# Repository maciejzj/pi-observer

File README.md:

# pi-observer
A system for remote control, data acquisition and visualization for Raspberry Pi.

WIP: Moving from PHP based web stack to Pyton Flask.

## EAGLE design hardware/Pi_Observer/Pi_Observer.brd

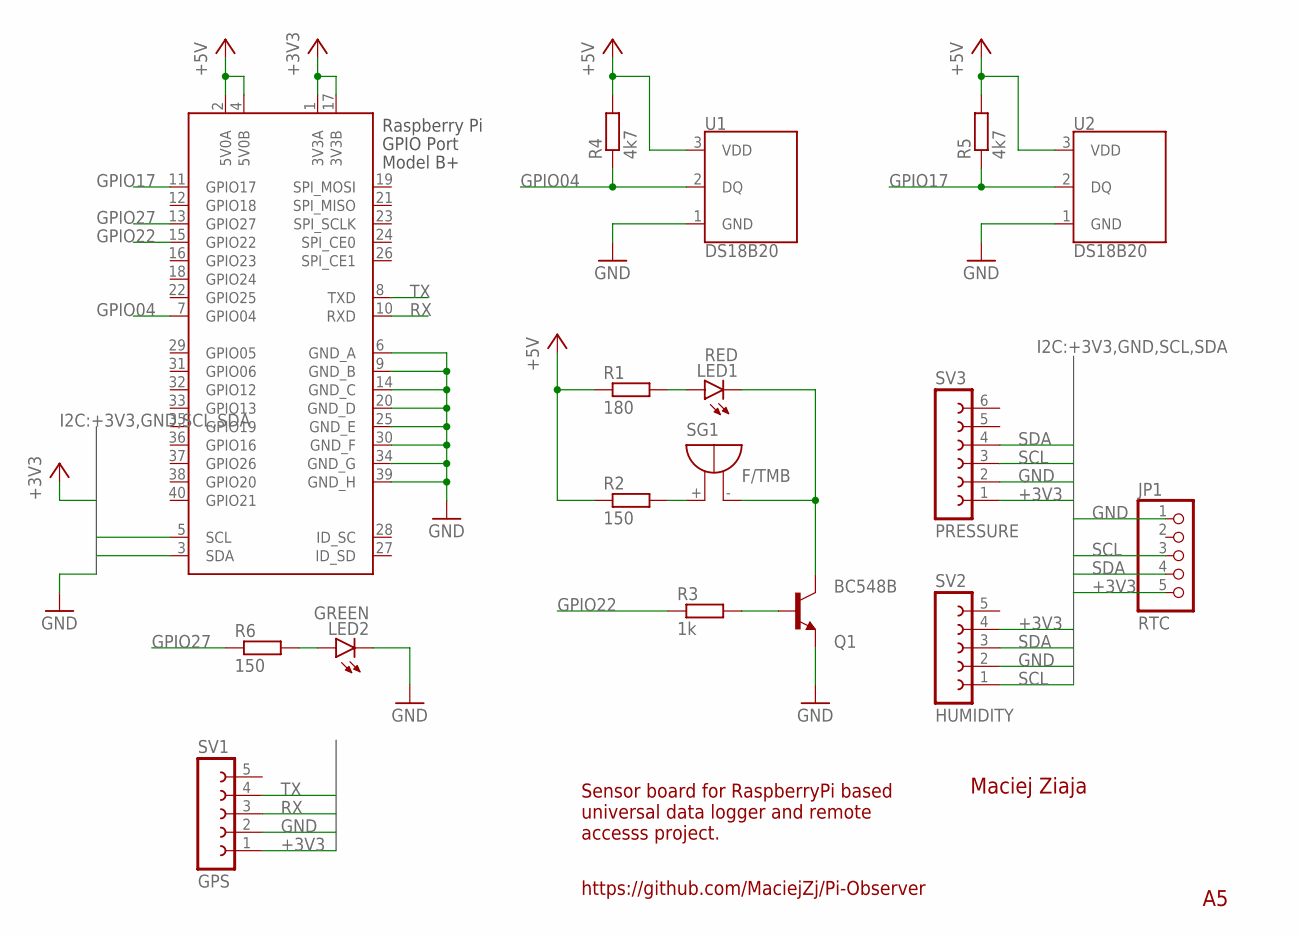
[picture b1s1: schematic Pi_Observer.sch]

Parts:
JP1: RTC; 1X05
LED1: RED; LED5MM
LED2: GREEN; LED5MM
Q1: BC548B; TO92-EBC
R1: 180; M1206
R2, R6: 150; M1206
R3: 1k; M1206
R4, R5: 4k7; M1206
SG1: F/TMB
SV1: GPS; FE05-1
SV2: HUMIDITY; FE05-1
SV3: PRESSURE; FE06
U1, U2: DS18B20; TO-92-AMMO
X1: RASPI_GPIO_B+#_PIN; RASPI_GPIO_B+_PIN

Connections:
+3V3: JP1.5, SV1.1, SV2.4, SV3.1, X1.1 (3V3A), X1.17 (3V3B)
+5V: R1.1, R2.1, R4.2, R5.2, U1.3 (VDD), U2.3 (VDD), X1.2 (5V0A), X1.4 (5V0B)
GND: JP1.1, LED2.K (C), Q1.E, SV1.2, SV2.2, SV3.2, U1.1 (GND), U2.1 (GND), X1.6 (GND_A), X1.9 (GND_B), X1.14 (GND_C), X1.20 (GND_D), X1.25 (GND_E), X1.30 (GND_F), X1.34 (GND_G), X1.39 (GND_H)
GPIO04: R4.1, U1.2 (DQ), X1.7 (GPIO04)
GPIO17: R5.1, U2.2 (DQ), X1.11 (GPIO17)
GPIO22: R3.1, X1.15 (GPIO22)
GPIO27: R6.1, X1.13 (GPIO27)
unnamed: LED1.K (C), Q1.C, SG1.-
unnamed: R2.2, SG1.+
unnamed: LED1.A, R1.2
unnamed: Q1.B, R3.2
unnamed: LED2.A, R6.2
RX: SV1.3, X1.10 (RXD)
SCL: JP1.3, SV2.1, SV3.3, X1.5 (SCL)
SDA: JP1.4, SV2.3, SV3.4, X1.3 (SDA)
TX: SV1.4, X1.8 (TXD)

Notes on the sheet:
Maciej Ziaja
https://github.com/MaciejZj/Pi-Observer
Sensor board for RaspberryPi based universal data logger and remote accesss project.

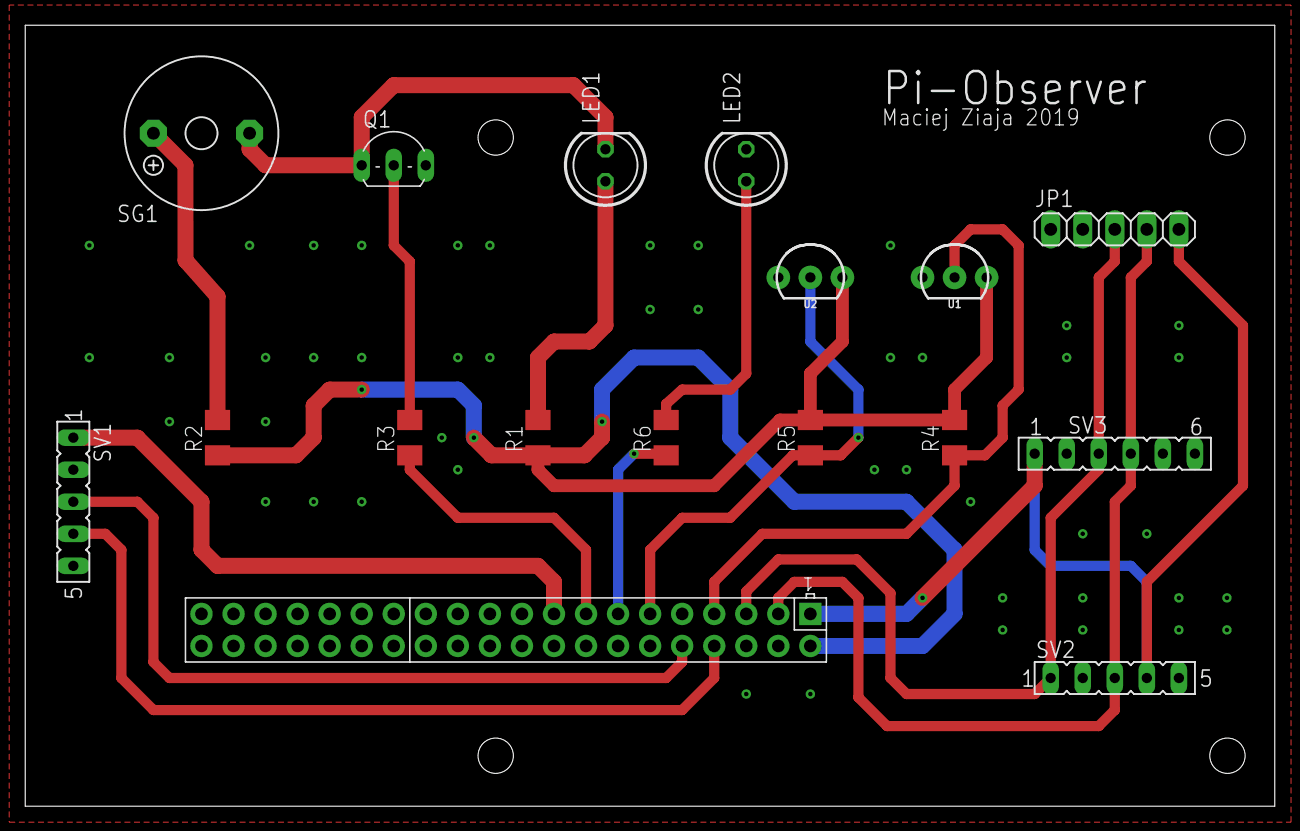
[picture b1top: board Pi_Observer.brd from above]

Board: 2 copper layers, 99.0 x 61.9 mm, 17 parts (0 on the bottom side), 16 nets.

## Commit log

2018-10-09 Imports hitherto work
2018-10-09 Creates README and .gitignore
2018-10-12 Update README.md
    Changed description of the project.
2018-10-13 Create db_setup and adds users db creation
2018-10-14 Install python sql module and setup db for logs
2018-10-14 Log pressure to sql db
2018-10-14 Log from thermometers using Python
2018-10-14 Log temperature to sql db
2018-10-14 Fix timestamp format for press alt db logging
2018-10-14 Log location to sql db
    Although this provides sql db logging functionality for all sensors, the
    gps.py is left in a messy state between old way of logging and new, iss14
    and iss11 are likely to address this problem.
    Closes: #6
2018-10-15 Remove old way of location logging
2018-10-15 Cleanup gps class
    Although this resolves cleanup issue the class may still need better error
    handling
    Resolves: #14
2018-10-15 Create separate dbs for users and sensor logs
2018-10-15 reapaired lack of semicolon - db_setup.sql -line 12 added second author's name - html/index.php created html/register.php
2018-10-16 registration with e-mail - frontend changed html/main.php - added second author's name
2018-10-16 users table in balloonS_users db changed
2018-10-16 repair - 3
2018-10-16 Display temperature log as html table
    Keep in mind that the table in not stylised so it has no borders and
    whats more important it is as long as it needs to display all records.
2018-10-16 Shorten creating tables and clean the clode
2018-10-16 Create css for tables to limit their height
2018-10-16 Move creating table to func in and make univerasal
    The function is in separate file, tables names are stored in dictionary,
    applied this method of making tables to all logs.
    Resolves: #8
2018-10-16 Import introduction report
2018-10-16 Update report of Maciej Ziaja for W2
2018-10-16 Add registration by e-mail
2018-10-18 Cleaning folders structure after report
2018-10-20 Pass JSON temp_log table from php to js
    This is clumsy now. Better way may be preparing data before drawing the
    site, then deploying it by echo() and innerHTML.
2018-10-20 Registration polish
2018-10-20 Separate making log tables and displaying them
    This enables us to process the data and pass it to js at the beggining
    of the file, instead of doing it in the middle of html site.
2018-10-20 Repair of email_confirmation.php and welcome.php
2018-10-20 Pass all logs with JSON
2018-10-21 Add forgotten hum_log JSON passing
2018-10-21 Create func for extracting plot data from JSON
2018-10-21 Create chart drawing function for hum log
2018-10-23 Maciej Ziaja report W3 and minor fixes
2018-10-23 Maciej Cholewa report W3
2018-10-28 Add double chart making for temperature
    Also ensures that internal and external temperatures are logged with
    same timestamp.
2018-10-28 Draw all charts with js
2018-10-28 Remove old way of presenting logs data
2018-10-28 Better errors handling in gps communication
2018-10-28 Add status field to location logging
2018-10-28 Extract loc data from JSON to arrays
2018-10-28 Draw google maps markers from SQL db logs
    Resolves: #22
2018-10-28 Temporary update charts css
    This will be polished in the future
2018-10-31 Stylise log tables
    This moves css to the less framework
2018-11-01 Consistent blue accent color
2018-11-01 Stylise Google Maps box
2018-11-01 Remove old buttons for downloading log files
2018-11-01 Create borders and shadows for all charts
2018-11-01 Stylise motion stream div
2018-11-01 Fix make_table calling arguments
2018-11-06 Design the tables' and charts' position on site
2018-11-08 Create new look for topbar
2018-11-08 Add new style for login page
2018-11-08 Make corners inside google maps round
2018-11-09 Cleanup the topbar
2018-11-09 Strip css for future responsive rewriting
2018-11-09 Rearrange css code order
2018-11-09 Add control panel container and description
2018-11-09 Make wrapper for gpio and strip stream css
2018-11-09 Responsive layout for single tab sections
2018-11-09 Responsvie layout for maps and controls
2018-11-09 Responsive layout for temp log
2018-11-09 Add padding for footer
2018-11-10 Fold time cell in loc table
2018-11-10 Make tablet layout for gpio and stream
2018-11-10 Remove unnecessary map canvas css wrapper
2018-11-10 Fix stream height to preserve placeholder dimensions
2018-11-10 Mobile version for charts and tables
2018-11-10 Change min width of site and fix typo
2018-11-10 Add viewport for mobile screen support
    Resolves: #29
2018-11-11 Add background svg to gpio buttons pane
2018-11-12 Apply new design to registration page
2018-11-13 Back to previous login page design
2018-11-13 Repair the orthography
2018-11-13 Add rocket to the bg graphic
2018-11-20 Make new GPIO buttons
2018-11-20 Adjust onclick on GPIO buttons
2018-11-27 Repair GPIO on off indicating
2018-11-27 Repair GPIO
2018-12-02 Repair GPIO 2
2019-01-15 Comment code
2019-01-15 Add comments to MZ part
2019-08-01 Move all comde to subfolder
2019-08-01 Add i2c setup in install script
2019-08-01 Update gitignore
2019-08-01 Add db setup, pklist and pip to install script
2019-08-02 Add hum sensor setup
2019-08-02 Update script to read from hum sensor
2019-08-02 Update temp sensor and 1 wire setup
    Also spaces in python scripts
2019-08-02 Extend 1wire setup
2019-08-06 Better align for sql setup script
2019-08-06 Setup and script press and alt log
2019-08-11 Fix gps and make it py3
2019-08-11 Add gps to installation
2019-08-11 Cleanup
2019-08-11 Fix unit in hum logger
2019-08-11 Round some log values
2019-08-11 Add rtc support and start script
2019-08-11 Fix RTC in start script
2019-08-12 Fix rtc_log location
2019-08-12 Fix date format in logs
2019-08-12 Bring chart drawer back
2019-08-12 Fix file naming and location
    Resolves: #32
2019-08-12 Extend start script
2019-08-16 Fix crontab
2019-08-16 Bring back web server
2019-08-20 Fix and setup gpio
2019-08-21 Bring back and setup camera
2019-08-23 Create schematic and board draft
2019-08-24 Enlarge motion frametate
2019-08-24 Update apt before install
2019-08-24 Update gitingore for eagle
2019-08-24 Advance board and chnage gpio pins
2019-08-31 Remove old name and sql dump
    Resolves: #26
2019-09-01 Fix Python indentation
    Resolves: #31
2019-09-01 Overall web code cleanup
    Warning: This shares ReCaptcha secret key, when fixing captcha
    for good the keys should be regenerated.
    Resolves: #41
    Resolves: #52
2019-09-01 Cleanup and remove email confirmation
2019-09-01 Further cleanup and deleting old stuff
2019-09-05 Fix and secure recaptcha keys
    Resolves: #51
2019-09-05 Move WiringPi installation to pkglist
    Resolves: #54
2019-09-05 Make topbar buttons text consistent
    Resolves: #53
2019-09-05 Fix more text and buttons
2019-09-05 Add install reboot prompt and silence cront msg
    Resolves: #55
2019-09-06 Add motion and sql cleanup
    Resolves: #50
    Resolves: #23
2019-09-06 Change main script name
    Resolves: #56
2019-09-06 Fix root msg in main script
2019-09-06 Remove confirmation code
    Resolves: #57
2019-09-06 Finish pcb design
    Resolves: #47
2019-09-06 Rm old pcb files
2019-09-07 Add paper sheet size on frame
2019-09-07 Fix pcb orientation
2019-09-07 Update Eagle proj version
2020-08-17 Update pkglist
2020-08-21 Draft dash
2020-08-21 Draft GPIO and stream
2020-08-21 Draft login form
2020-08-26 Clean up and add user login
2020-08-30 Add base styling for dashboard
2020-08-31 Embed dash in flask
2020-08-31 Draft dash tabs and more navs
2020-08-31 Clean up templates
2020-09-01 Better error handling for login
2020-09-01 Small layout cleanup
2020-09-01 Refactor temp sensor logger
2020-09-01 Refactor hum sensor logger
2020-09-01 Refactor press alt logger

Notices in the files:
parts and their libraries:
SparkFun-Sensors: Licensing: Creative Commons ShareAlike 4.0 International - https://creativecommons.org/licenses/by-sa/4.0
